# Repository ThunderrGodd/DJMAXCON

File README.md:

cotroller for PC rhythm games, based on vial-qmk

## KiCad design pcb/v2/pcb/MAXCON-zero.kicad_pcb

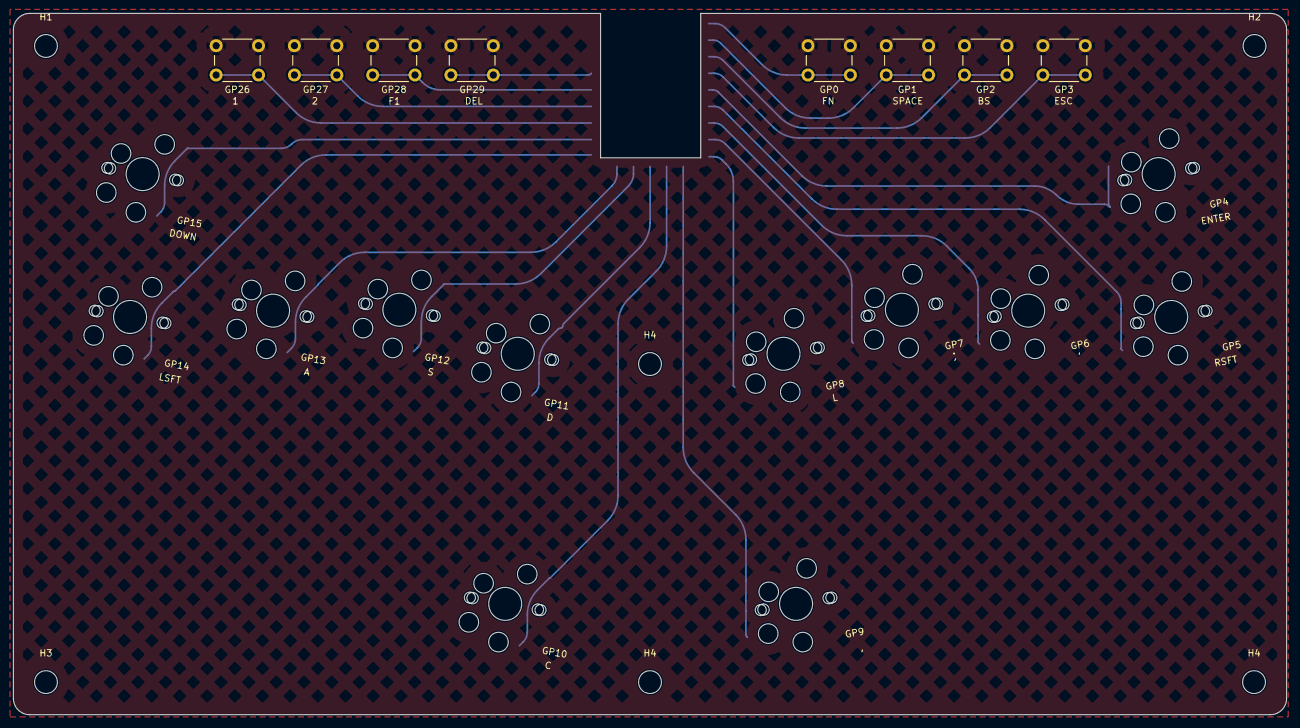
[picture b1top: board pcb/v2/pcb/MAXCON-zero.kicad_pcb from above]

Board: 2 copper layers, 195.3 x 107.6 mm, 27 parts (0 on the bottom side), 21 nets.

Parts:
GP0, GP1, GP2, GP3, GP26, GP27, GP28, GP29: SW_SPST; SW_PUSH_6mm
GP4, GP5, GP14, GP15: SW_SPST; SW_MXchocV2_HS_1.25u
GP6, GP7, GP8, GP11, GP12, GP13: SW_SPST; SW_MXchocV2_HS_1u
GP9, GP10: SW_SPST; SW_MXchocV2_HS_1.5u
H1, H2, H3, H4, H4#2, H4#3: MountingHole; MountingHole_3.5mm
RZ1: RP2040-Zero; RP2040-Zero (1)

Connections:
GND: GP0.2 (B), GP1.2 (B), GP2.2 (B), GP3.2 (B), GP4.2 (B), GP5.2 (B), GP6.2 (B), GP7.2 (B), GP8.2 (B), GP9.2 (B), GP10.1 (A), GP11.1 (A), GP12.1 (A), GP13.1 (A), GP14.1 (A), GP15.1 (A), GP26.2 (B), GP27.2 (B), GP28.2 (B), GP29.2 (B), RZ1.22 (GND)
unnamed: GP0.1 (A), RZ1.1 (GP0)
unnamed: GP1.1 (A), RZ1.2 (GP1)
unnamed: GP2.1 (A), RZ1.3 (GP2)
unnamed: GP3.1 (A), RZ1.4 (GP3)
unnamed: GP4.1 (A), RZ1.5 (GP4)
unnamed: GP5.1 (A), RZ1.6 (GP5)
unnamed: GP6.1 (A), RZ1.7 (GP6)
unnamed: GP7.1 (A), RZ1.8 (GP7)
unnamed: GP8.1 (A), RZ1.9 (GP8)
unnamed: GP9.1 (A), RZ1.10 (GP9)
unnamed: GP10.2 (B), RZ1.11 (GP10)
unnamed: GP11.2 (B), RZ1.12 (GP11)
unnamed: GP12.2 (B), RZ1.13 (GP12)
unnamed: GP13.2 (B), RZ1.14 (GP13)
unnamed: GP14.2 (B), RZ1.15 (GP14)
unnamed: GP15.2 (B), RZ1.16 (GP15)
unnamed: GP26.1 (A), RZ1.17 (GP26)
unnamed: GP27.1 (A), RZ1.18 (GP27)
unnamed: GP28.1 (A), RZ1.19 (GP28)
unnamed: GP29.1 (A), RZ1.20 (GP29)

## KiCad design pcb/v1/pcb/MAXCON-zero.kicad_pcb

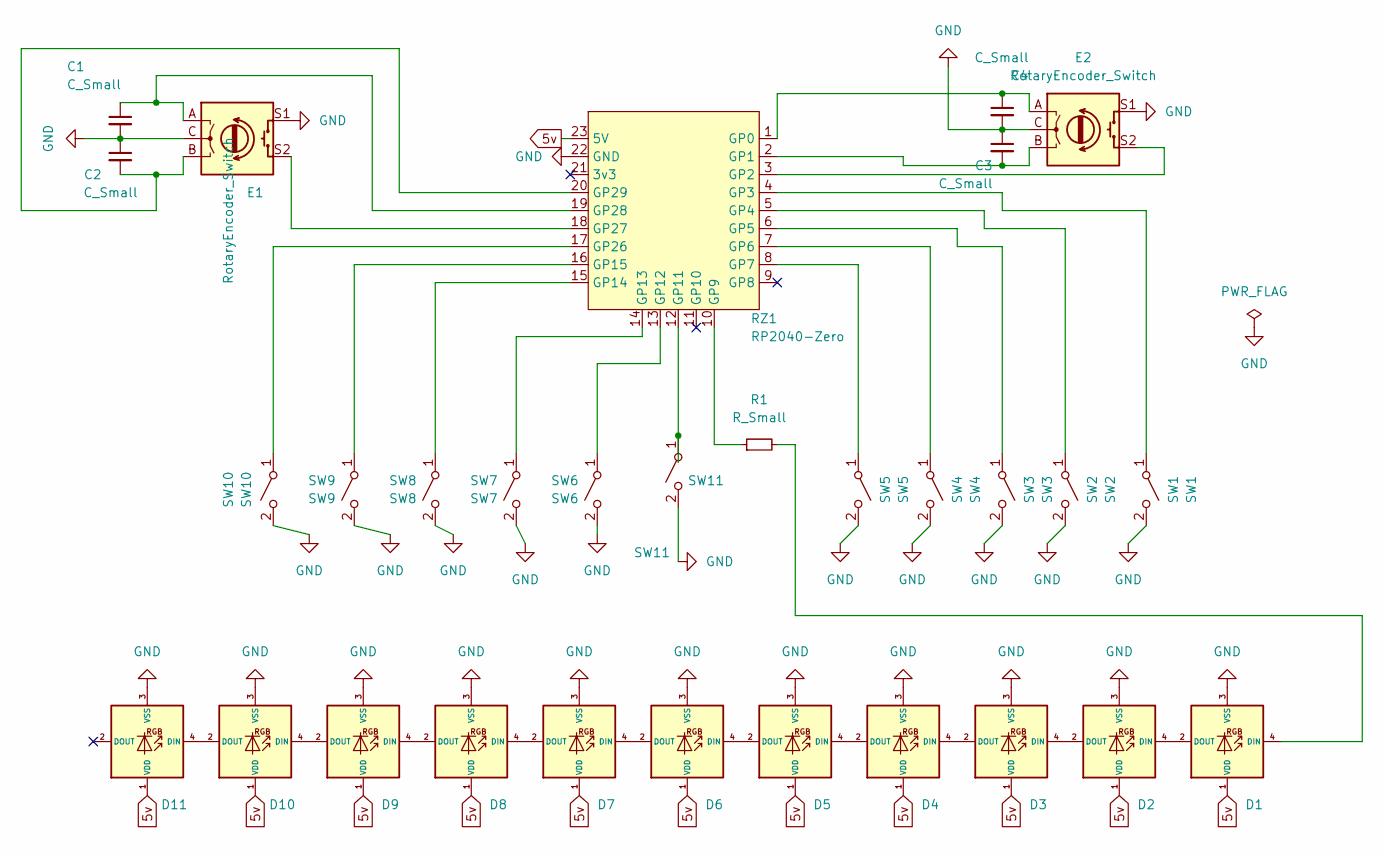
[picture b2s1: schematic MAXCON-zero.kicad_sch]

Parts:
C1, C2, C3, C4: C_Small; C_0603_1608Metric
D1, D2, D3, D4, D5, D6, D7, D8, D9, D10, D11: SK6812MINI-E; SK6812MINI_3535_6028_3.2x2.8mm_Round; MPN SK812MINI-E
E1, E2: RotaryEncoder_Switch; RotaryEncoder_Alps_EC11E-Switch_Vertical_H20mm_CircularMoun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
R1: R_Small; R_THT_5.08mm_Horizontal
RZ1: RP2040-Zero; RP2040-Zero (1)
SW1: SW1; MCX100
SW2: SW2; MCX100
SW3: SW3; MCX100
SW4: SW4; MCX100
SW5: SW5; MCX100
SW6: SW6; MCX100
SW7: SW7; MCX100
SW8: SW8; MCX100
SW9: SW9; MCX100
SW10: SW10; MCX100
SW11: SW11; MCX100

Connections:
5v: D1.1 (VDD), D2.1 (VDD), D3.1 (VDD), D4.1 (VDD), D5.1 (VDD), D6.1 (VDD), D7.1 (VDD), D8.1 (VDD), D9.1 (VDD), D10.1 (VDD), D11.1 (VDD), RZ1.23 (5V)
GND: C1.2, C2.1, C3.1, C4.2, D1.3 (VSS), D2.3 (VSS), D3.3 (VSS), D4.3 (VSS), D5.3 (VSS), D6.3 (VSS), D7.3 (VSS), D8.3 (VSS), D9.3 (VSS), D10.3 (VSS), D11.3 (VSS), E1.C, E1.S1, E2.C, E2.S1, RZ1.22 (GND), SW1.2 (B), SW2.2 (B), SW3.2 (B), SW4.2 (B), SW5.2 (B), SW6.2 (B), SW7.2 (B), SW8.2 (B), SW9.2 (B), SW10.2 (B), SW11.2 (B)
unnamed: C2.2, E1.B, RZ1.20 (GP29)
unnamed: C3.2, E2.B, RZ1.2 (GP1)
unnamed: C4.1, E2.A, RZ1.1 (GP0)
unnamed: D1.2 (DOUT), D2.4 (DIN)
unnamed: D1.4 (DIN), R1.2
unnamed: D2.2 (DOUT), D3.4 (DIN)
unnamed: D3.2 (DOUT), D4.4 (DIN)
unnamed: D4.2 (DOUT), D5.4 (DIN)
unnamed: D5.2 (DOUT), D6.4 (DIN)
unnamed: D6.2 (DOUT), D7.4 (DIN)
unnamed: D7.2 (DOUT), D8.4 (DIN)
unnamed: D8.2 (DOUT), D9.4 (DIN)
unnamed: D10.2 (DOUT), D11.4 (DIN)
unnamed: D9.2 (DOUT), D10.4 (DIN)
unnamed: E1.S2, RZ1.18 (GP27)
unnamed: E2.S2, RZ1.3 (GP2)
unnamed: R1.1, RZ1.10 (GP9)
unnamed: RZ1.4 (GP3), SW1.1 (A)
unnamed: RZ1.5 (GP4), SW2.1 (A)
unnamed: RZ1.6 (GP5), SW3.1 (A)
unnamed: RZ1.7 (GP6), SW4.1 (A)
unnamed: RZ1.8 (GP7), SW5.1 (A)
unnamed: RZ1.12 (GP11), SW11.1 (A)
unnamed: RZ1.13 (GP12), SW6.1 (A)
unnamed: RZ1.14 (GP13), SW7.1 (A)
unnamed: RZ1.15 (GP4), SW8.1 (A)
unnamed: RZ1.16 (GP3), SW9.1 (A)
unnamed: RZ1.17 (GP19), SW10.1 (A)
unnamed: C1.1, E1.A, RZ1.19 (GP28)

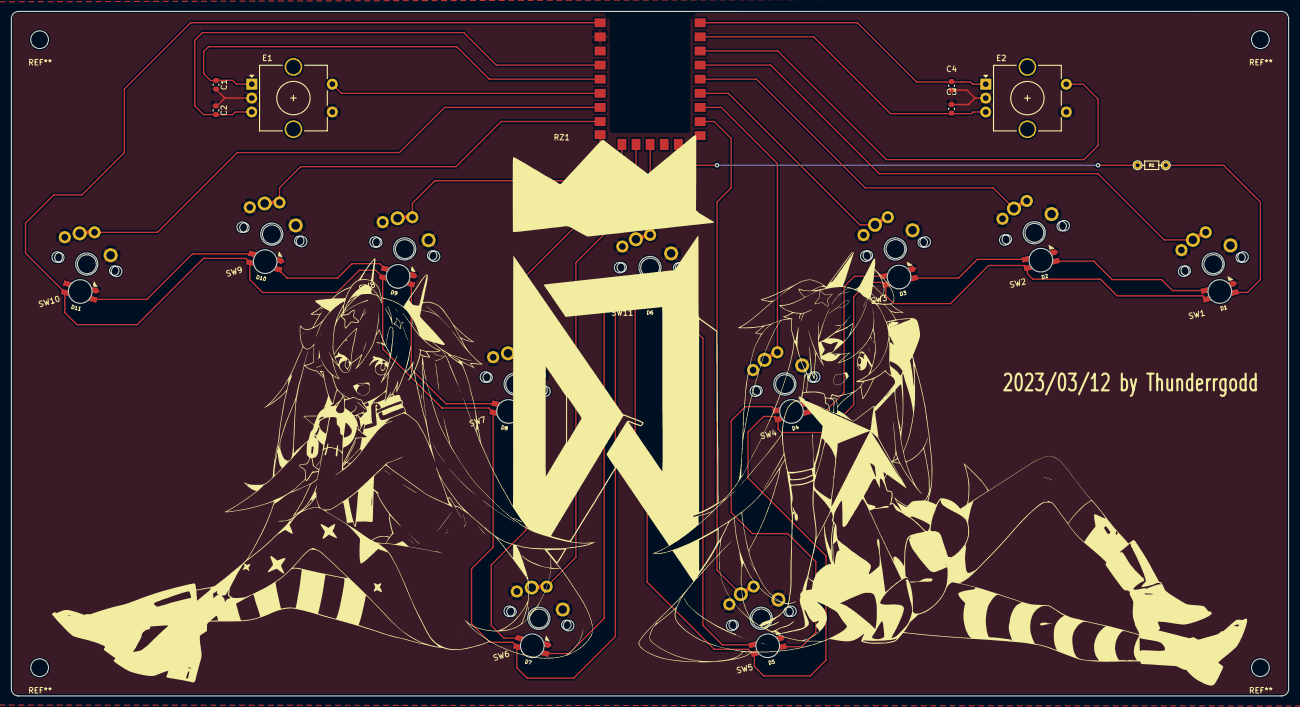
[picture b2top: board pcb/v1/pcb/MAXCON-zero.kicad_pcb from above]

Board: 2 copper layers, 229.9 x 123.2 mm, 31 parts (0 on the bottom side), 31 nets.

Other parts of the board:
2023/03/12 by Thunderrgodd: LOGO; hnm

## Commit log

2023-04-04 Create pcb
2025-07-21 added v2
2025-07-21 added case readme
